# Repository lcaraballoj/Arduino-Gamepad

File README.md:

# Arduino-Gamepad
A USB gamepad made from an Arduino Pro Micro that I developed into a soldering workshop in the Fall of 2020 to Fall 2021.

# Table of Contents
1. [Description](#description)
2. [Materials](#materials)
3. [Libraries Needed](#libraries-needed)
5. [Assembly Steps](#assembly-steps)

# Description
This workshop allows attendees to make their own game controller out of an Arduino, custom PCBs, buttons, and a joystick. It will teach about soldering, specifically through hole soldering. We use custom PCBs to eliminate the need for wires and make it eaiser for first solderers. It will also introduce the participants to Arduino code and libraries, although they will not code, it is important to do a quick overview of the code so that they understand why their game controller works. The goal of this workshop is to introduce attendees to Arduinos, soldering, solder safety, PCBs, and for them to walk away with a cool game controller that they personally made. 

# Materials
1. Arduino Pro Micro
2. Custom PCBs (main PCB and button PCB)
3. 4 Tactile Button Switches
4. USB Cable
5. Joystick
6. Soldering Iron
7. Solder
8. Custom Case

# Libraries Needed
1. [Keyboard by Arduino](https://www.arduino.cc/reference/en/libraries/keyboard/)
2. [Mouse by Arduino](https://www.arduino.cc/reference/en/libraries/mouse/)

# Assembly Steps
1. Place Arduino header pins and arduino on PCB.
2. Flip over PCB so that you can solder the header pins to the PCB board.
3. Solder header pins to Arduino.
9. Solder joystick.
10. Solder female header pin extender.
11. Solder buttons onto Button PCB.
12. Solder header pin, with long side on the bottom to the Button PCB.
13. Put the two PCBs together.
14. Check circuit and upload code to test
15. Create/put in casing
16. Once in case test again to make sure everything is operational

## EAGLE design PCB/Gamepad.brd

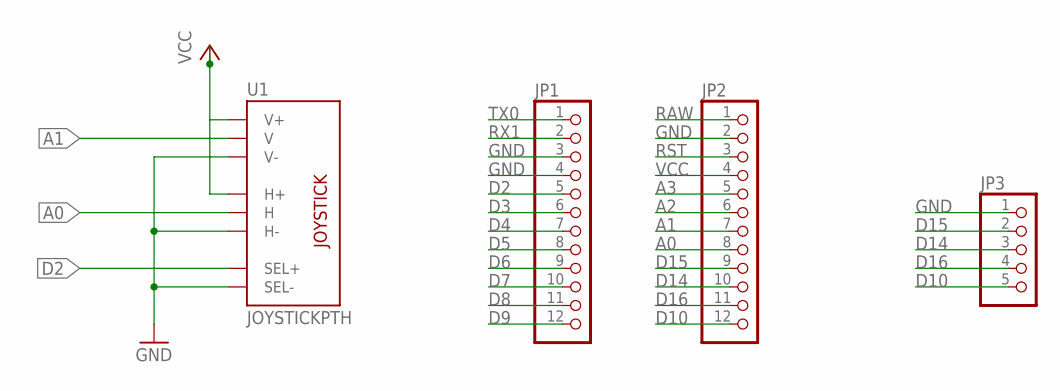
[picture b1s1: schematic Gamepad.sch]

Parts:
JP1, JP2: PINHD-1X12; 1X12
JP3: PINHD-1X5; 1X05
U1: JOYSTICKPTH; JOYSTICK

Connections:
A0: JP2.8, U1.H2 (H)
A1: JP2.7, U1.V2 (V)
A2: JP2.6
A3: JP2.5
D2: JP1.5, U1.B1A (SEL+)
D3: JP1.6
D4: JP1.7
D5: JP1.8
D6: JP1.9
D7: JP1.10
D8: JP1.11
D9: JP1.12
D10: JP2.12, JP3.5
D14: JP2.10, JP3.3
D15: JP2.9, JP3.2
D16: JP2.11, JP3.4
GND: JP1.3, JP1.4, JP2.2, JP3.1, U1.B2A (SEL-), U1.H3 (H-), U1.V3 (V-)
RAW: JP2.1
RST: JP2.3
RX1: JP1.2
TX0: JP1.1
VCC: JP2.4, U1.H1 (H+), U1.V1 (V+)

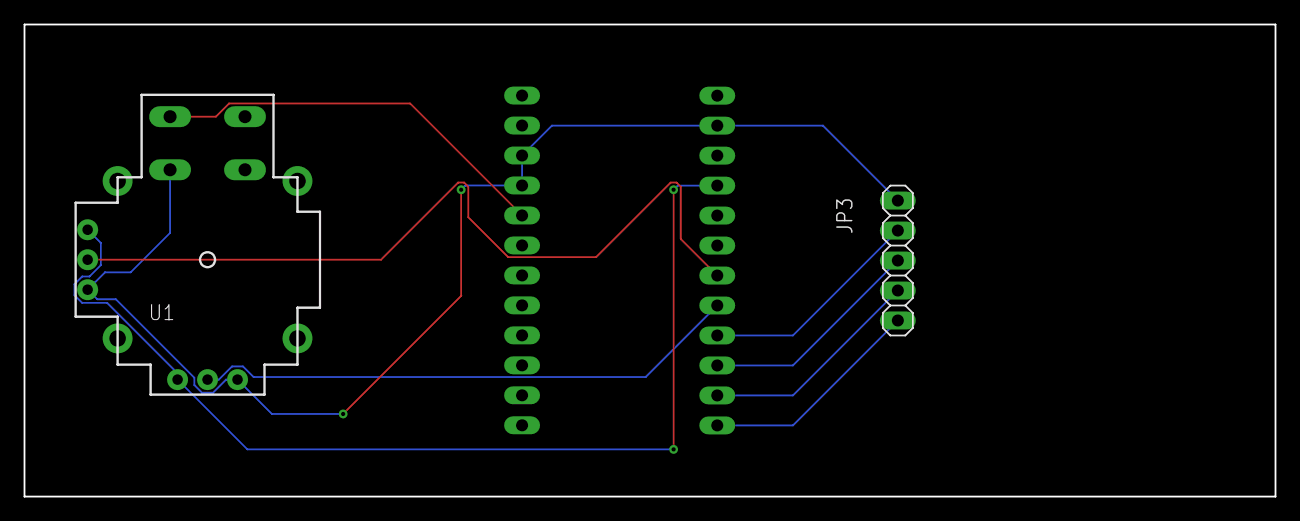
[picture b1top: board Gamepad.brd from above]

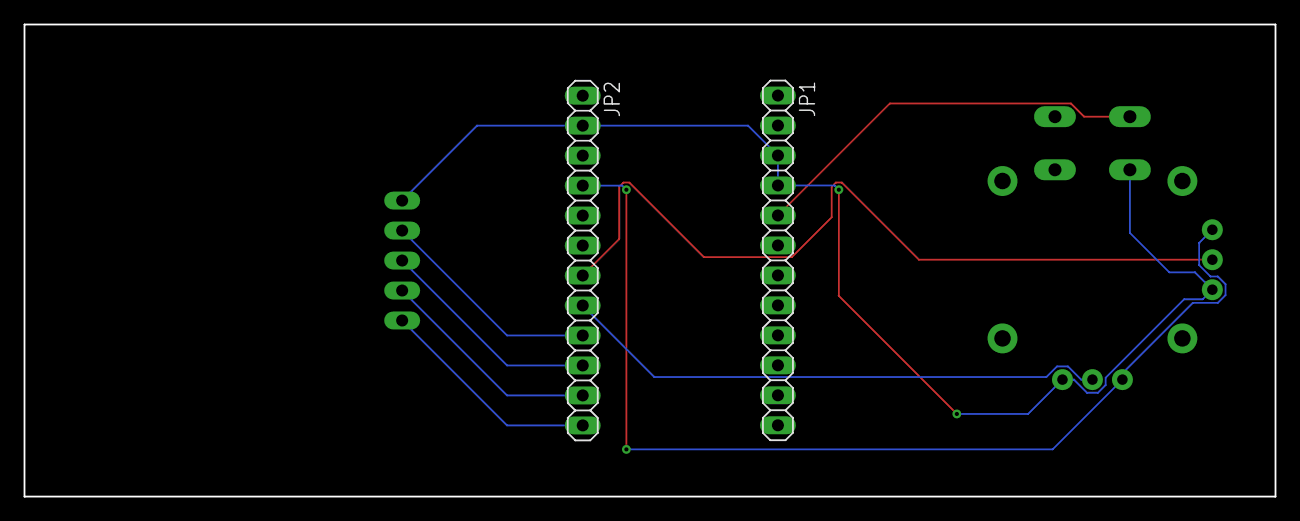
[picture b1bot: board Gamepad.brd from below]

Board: 2 copper layers, 106.0 x 40.0 mm, 4 parts (2 on the bottom side), 9 nets.

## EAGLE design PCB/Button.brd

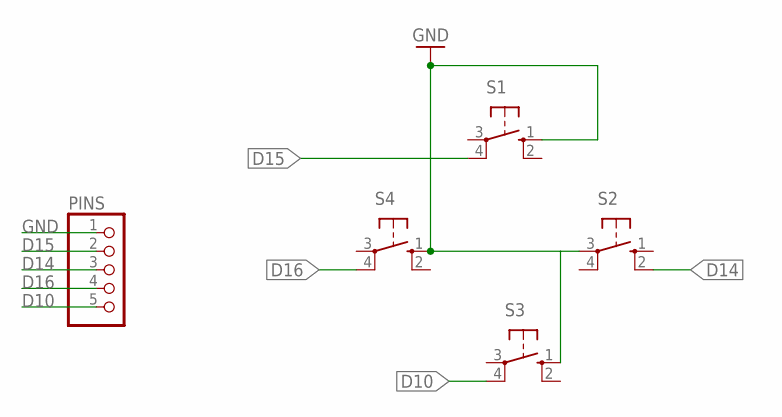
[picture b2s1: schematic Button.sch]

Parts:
PINS: PINHD-1X5; 1X05
S1, S2, S3, S4: 10-XX; B3F-10XX

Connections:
D10: PINS.5, S3.4 (P1)
D14: PINS.3, S2.2 (S1)
D15: PINS.2, S1.4 (P1)
D16: PINS.4, S4.4 (P1)
GND: PINS.1, S1.1 (S), S2.3, S3.1 (S), S4.1 (S)

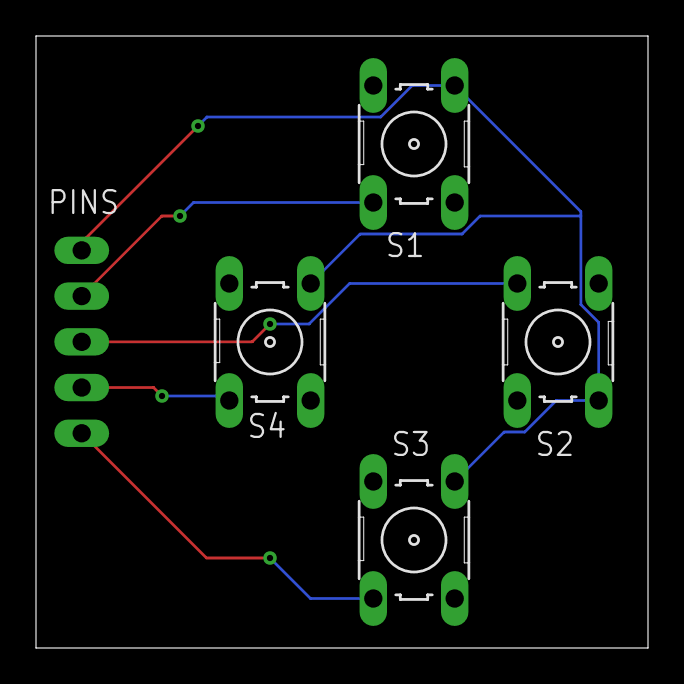
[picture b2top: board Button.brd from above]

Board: 2 copper layers, 34.0 x 34.0 mm, 5 parts (1 on the bottom side), 5 nets.

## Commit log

2021-07-09 Uploading documents and code
2022-05-12 Adding prototype pictures
2022-05-12 Adding pictures for prototypes
2022-05-12 Adding PCB
